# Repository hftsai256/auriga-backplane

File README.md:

# Auriga Backplane

The project is reverse-engineered from the original backplane to house dual 2.5" SSDs into one 3.5" HDD bay with
[this mounting bracket](https://www.corsair.com/us/en/p/pc-components-accessories/cssd-brkt2/dual-ssd-mounting-bracket-aca-a-black-cssd-brkt2).
All mechanical dimensions are hand-measured and "rounded to a reasonable factor in metric units."

# Known Issues

The pin layout of the LED connectors are reversed (as of v0.5.) Therefore one side of the ribbon cable must be
reversed in order to activate the LED indicators.

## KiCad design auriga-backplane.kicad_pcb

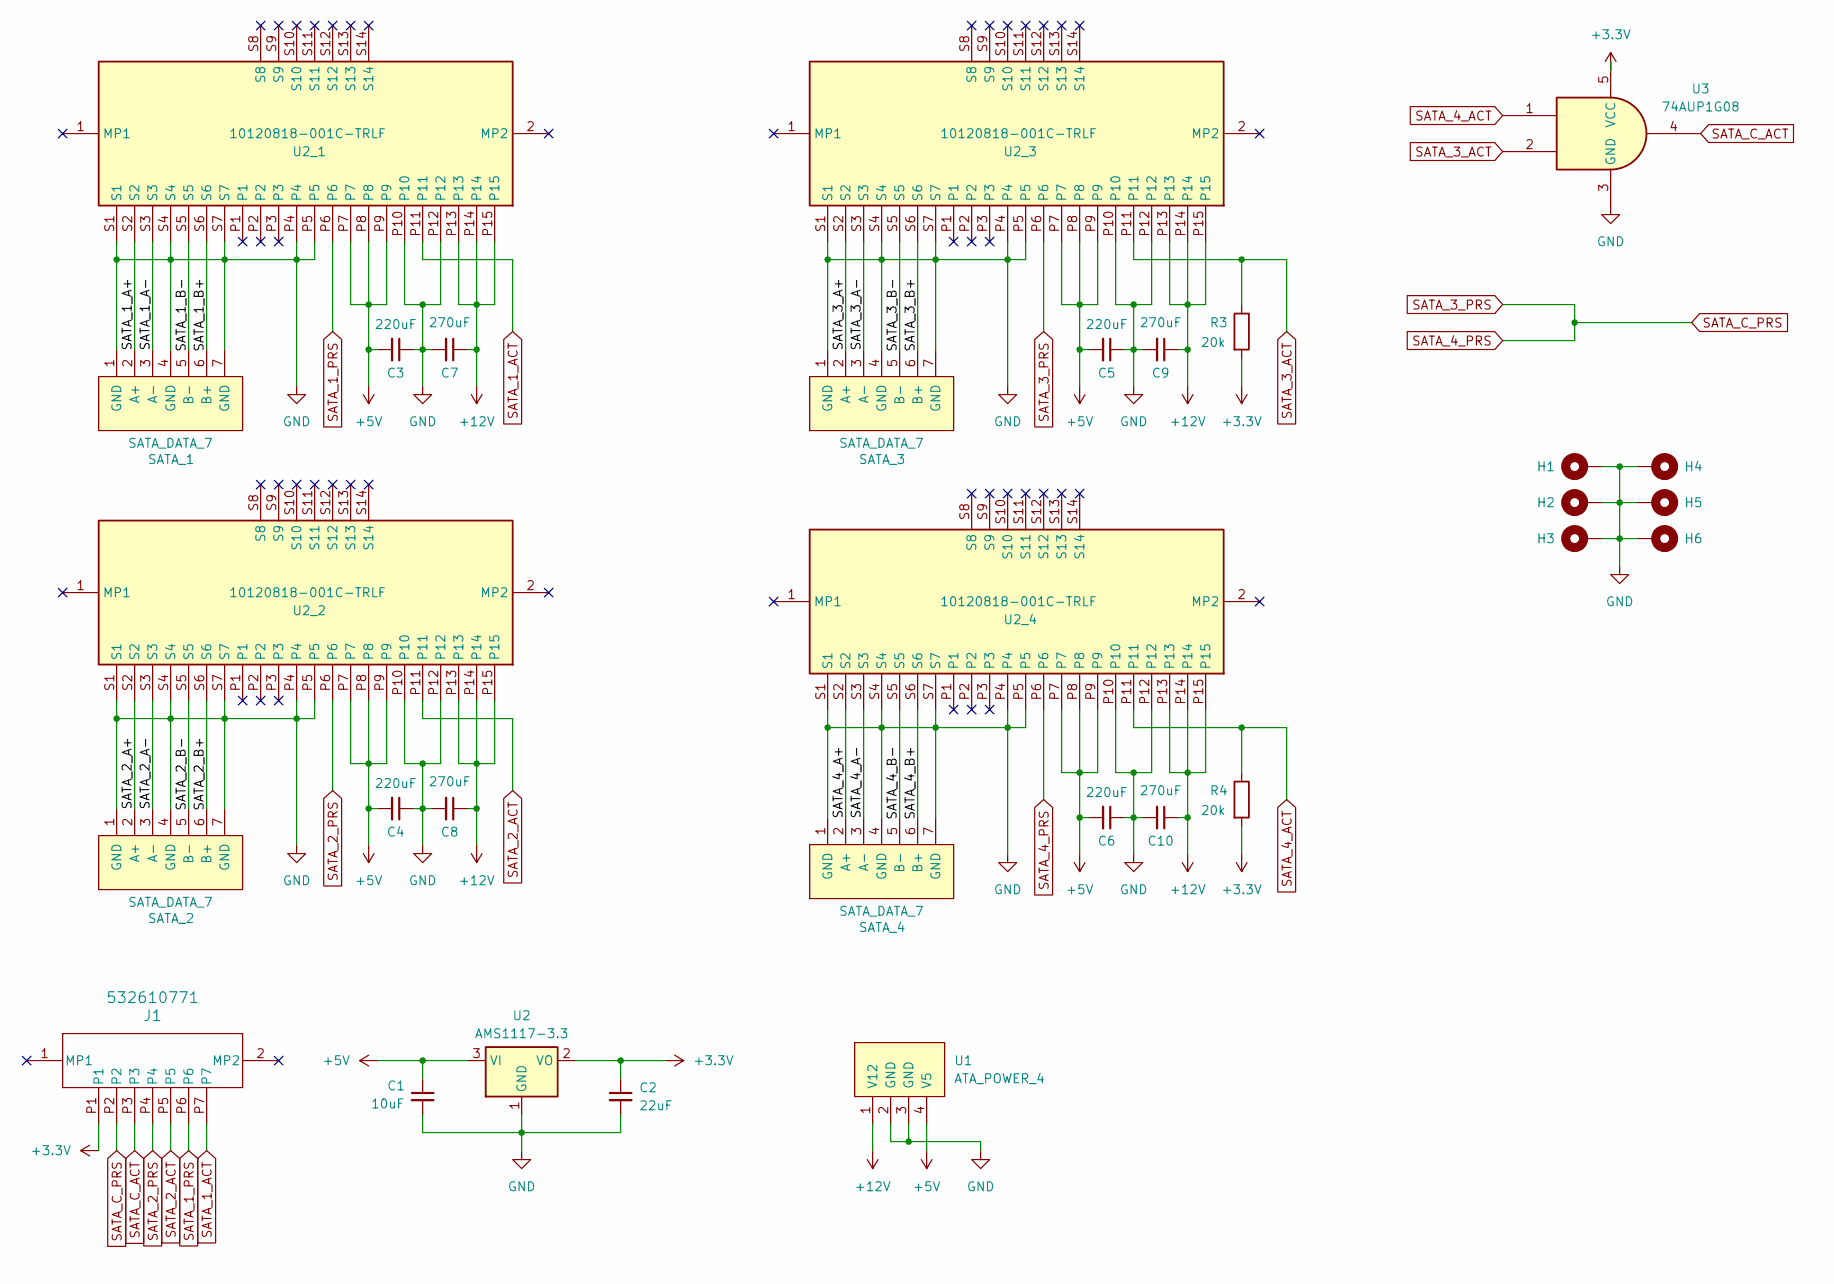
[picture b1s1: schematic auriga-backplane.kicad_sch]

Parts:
C1: 10uF; C_0805_2012Metric
C2: 22uF; C_0402_1005Metric
C3, C4, C5, C6: 220uF; C_1210_3225Metric_Pad1.33x2.70mm_HandSolder
C7, C8, C9, C10: 270uF; CP_Elec_6.3x7.7
H1, H2, H3, H4, H5, H6: MountingHole_Pad; MountingHole_3.7mm_Pad_TopBottom_Thin
J1: 532610771; CON_532610771
R3, R4: 20k; R_0402_1005Metric
SATA_1, SATA_2, SATA_3, SATA_4: SATA_DATA_7
U1: ATA_POWER_4
U2: AMS1117-3.3; SOT-223-3_TabPin2
U2_1, U2_2, U2_3, U2_4: 10120818-001C-TRLF; 10120818001CTRLF; Manufacturer_Part_Number 10120818-001C-TRLF
U3: 74AUP1G08; SOT-23-5

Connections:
+3.3V: C2.1, J1.P1, R3.2, R4.2, U2.2 (VO), U3.5 (VCC)
+5V: C1.1, C3.2, C4.2, C5.2, C6.2, U1.4 (V5), U2.3 (VI), U2_1.P7, U2_1.P8, U2_1.P9, U2_2.P7, U2_2.P8, U2_2.P9, U2_3.P7, U2_3.P8, U2_3.P9, U2_4.P7, U2_4.P8, U2_4.P9
+12V: C7.1, C8.1, C9.1, C10.1, U1.1 (V12), U2_1.P13, U2_1.P14, U2_1.P15, U2_2.P13, U2_2.P14, U2_2.P15, U2_3.P13, U2_3.P14, U2_3.P15, U2_4.P13, U2_4.P14, U2_4.P15
/SATA_1_A+: SATA_1.2 (A+), U2_1.S2
/SATA_1_A-: SATA_1.3 (A-), U2_1.S3
/SATA_1_B+: SATA_1.6 (B+), U2_1.S6
/SATA_1_B-: SATA_1.5 (B-), U2_1.S5
/SATA_2_A+: SATA_2.2 (A+), U2_2.S2
/SATA_2_A-: SATA_2.3 (A-), U2_2.S3
/SATA_2_B+: SATA_2.6 (B+), U2_2.S6
/SATA_2_B-: SATA_2.5 (B-), U2_2.S5
/SATA_3_A+: SATA_3.2 (A+), U2_3.S2
/SATA_3_A-: SATA_3.3 (A-), U2_3.S3
/SATA_3_B+: SATA_3.6 (B+), U2_3.S6
/SATA_3_B-: SATA_3.5 (B-), U2_3.S5
/SATA_4_A+: SATA_4.2 (A+), U2_4.S2
/SATA_4_A-: SATA_4.3 (A-), U2_4.S3
/SATA_4_B+: SATA_4.6 (B+), U2_4.S6
/SATA_4_B-: SATA_4.5 (B-), U2_4.S5
GND: C1.2, C2.2, C3.1, C4.1, C5.1, C6.1, C7.2, C8.2, C9.2, C10.2, H1.1, H2.1, H3.1, H4.1, H5.1, H6.1, SATA_1.1 (GND), SATA_1.4 (GND), SATA_1.7 (GND), SATA_2.1 (GND), SATA_2.4 (GND), SATA_2.7 (GND), SATA_3.1 (GND), SATA_3.4 (GND), SATA_3.7 (GND), SATA_4.1 (GND), SATA_4.4 (GND), SATA_4.7 (GND), U1.2 (GND), U1.3 (GND), U2.1 (GND), U2_1.P4, U2_1.P5, U2_1.P10, U2_1.P12, U2_1.S1, U2_1.S4, U2_1.S7, U2_2.P4, U2_2.P5, U2_2.P10, U2_2.P12, U2_2.S1, U2_2.S4, U2_2.S7, U2_3.P4, U2_3.P5, U2_3.P10, U2_3.P12, U2_3.S1, U2_3.S4, U2_3.S7, U2_4.P4, U2_4.P5, U2_4.P10, U2_4.P12, U2_4.S1, U2_4.S4, U2_4.S7, U3.3 (GND)
SATA_1_ACT: J1.P7, U2_1.P11
SATA_1_PRS: J1.P6, U2_1.P6
SATA_2_ACT: J1.P5, U2_2.P11
SATA_2_PRS: J1.P4, U2_2.P6
SATA_3_ACT: R3.1, U2_3.P11, U3.2
SATA_3_PRS: J1.P2, U2_3.P6, U2_4.P6
SATA_4_ACT: R4.1, U2_4.P11, U3.1
SATA_C_ACT: J1.P3, U3.4

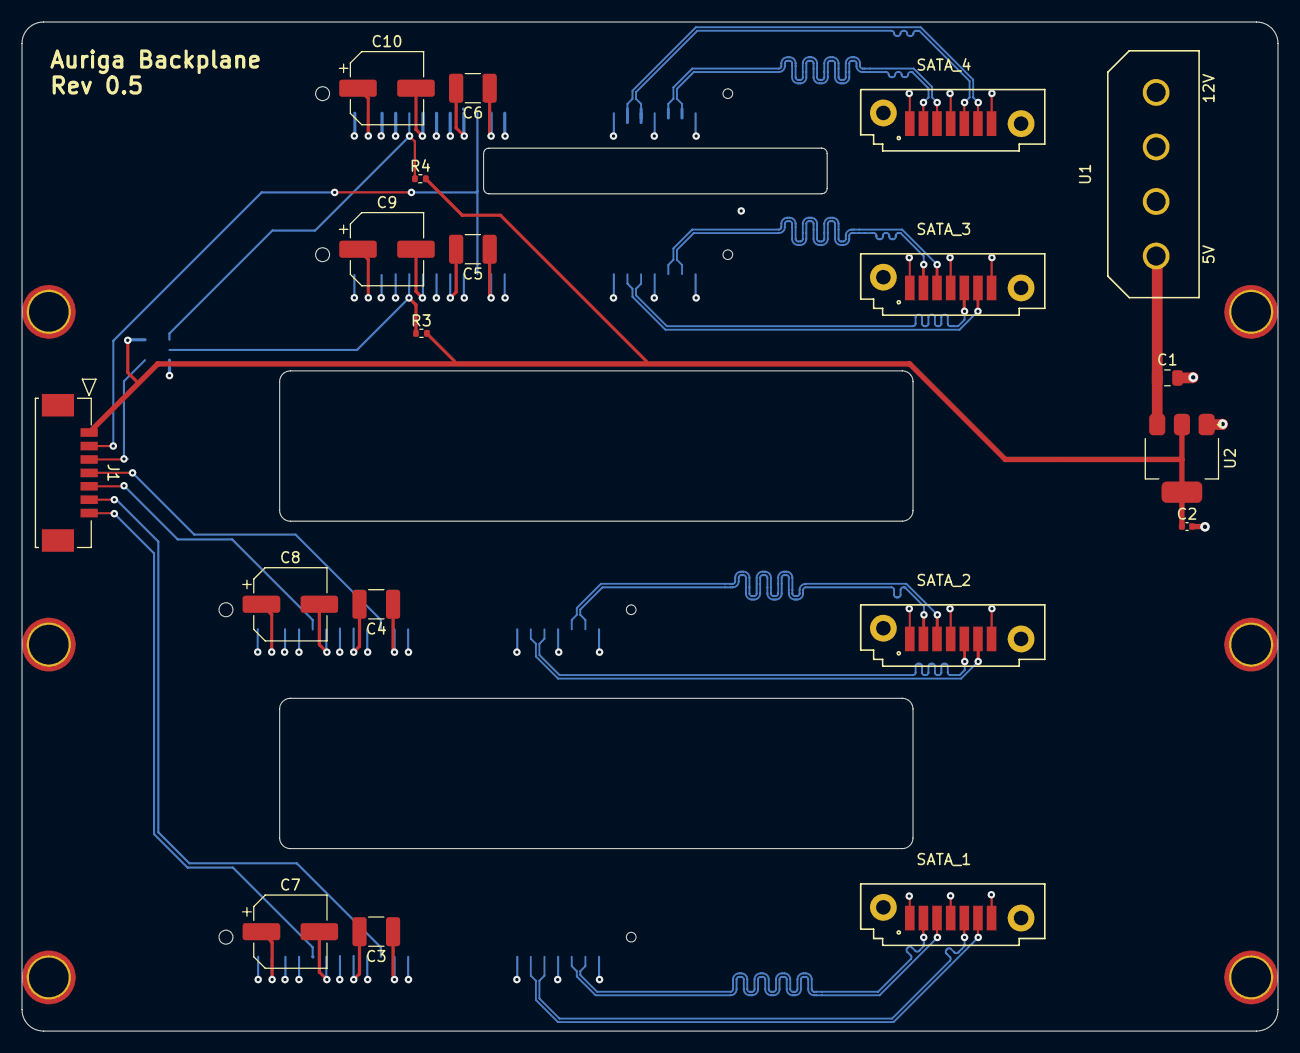
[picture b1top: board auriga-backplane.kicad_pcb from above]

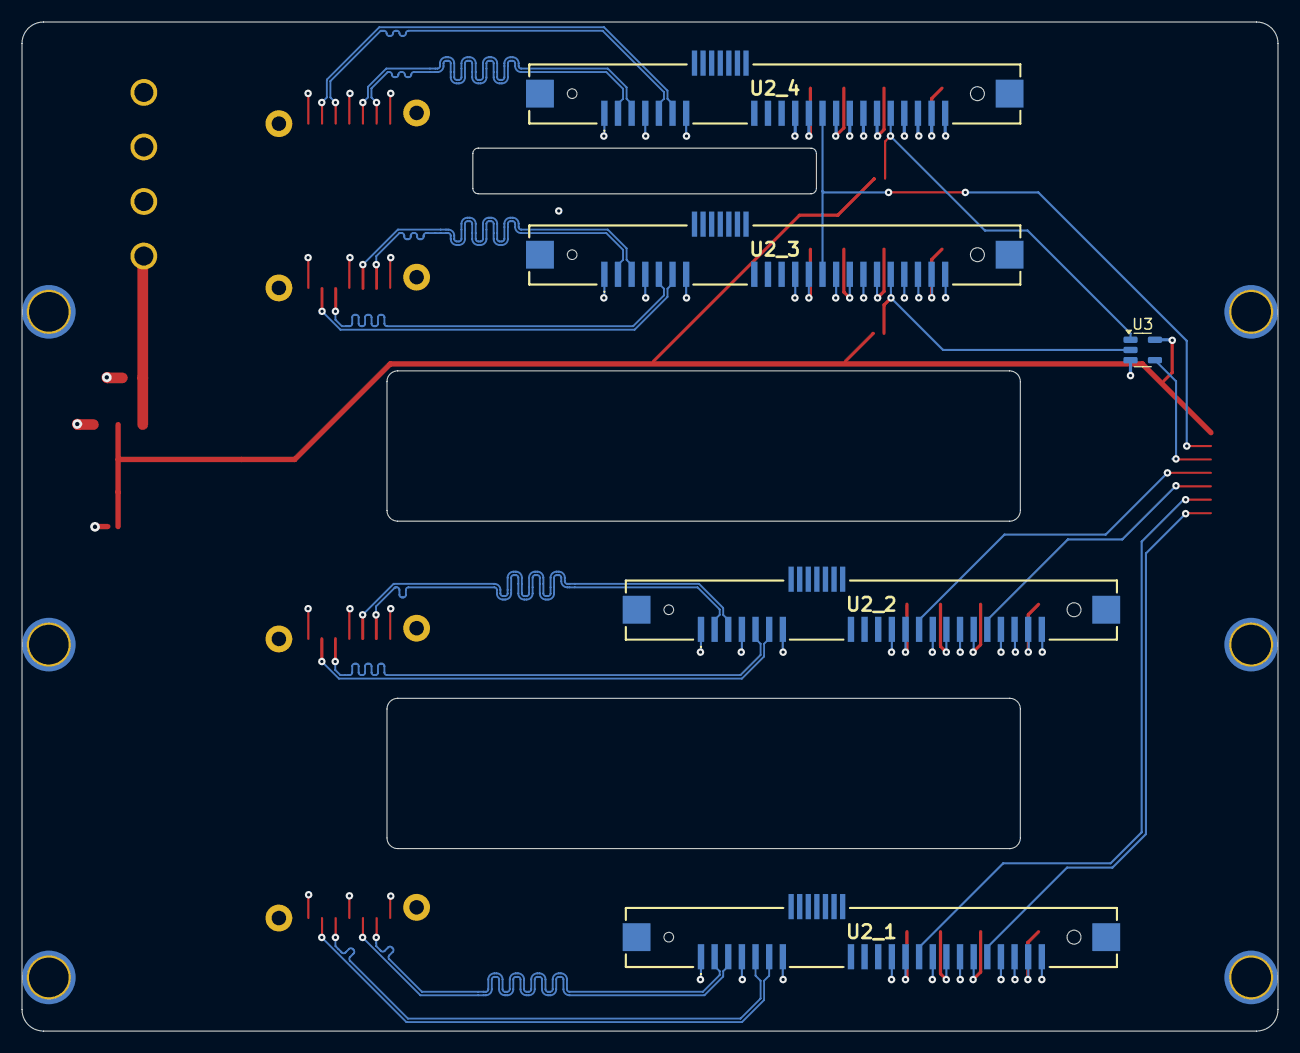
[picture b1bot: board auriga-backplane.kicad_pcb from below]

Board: 4 copper layers, 117.0 x 94.0 mm, 30 parts (5 on the bottom side), 28 nets.

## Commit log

2024-07-26 fixup! Initial commit
